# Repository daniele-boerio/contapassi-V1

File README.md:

# Setup Claude Code — contapassi

## Struttura del repo

```
contapassi/
├── .claude/
│   ├── CLAUDE.md                       ← contesto sempre caricato
│   └── skills/
│       ├── kicad-jlcpcb/SKILL.md
│       ├── nrf52840-firmware/SKILL.md
│       └── analisi-andatura/SKILL.md
├── .gitignore
├── README.md
│
├── docs/
│   ├── 01-design.md
│   ├── 02-bom-jlcpcb.md
│   ├── 03-firmware-taratura.md
│   └── datasheet/              ← E73, LSM6DSV16X, MCP73831, cella
│
├── hardware/
│   ├── contapassi.kicad_pro
│   ├── contapassi.kicad_sch
│   ├── contapassi.kicad_pcb
│   ├── lib/
│   │   ├── contapassi.kicad_sym
│   │   ├── contapassi.pretty/  ← footprint
│   │   └── 3dmodels/
│   └── production/
│       └── 2026-XX-XX-v1/      ← gerber + BOM + CPL di ogni ordine
│
├── firmware/
│   ├── CMakeLists.txt
│   ├── prj.conf
│   ├── boards/                 ← definizione board custom
│   └── src/
│
├── analysis/
│   ├── notebooks/
│   ├── src/                    ← parser, ZUPT, metriche
│   └── data/
│       ├── raw/                ← dump binari (NON versionati)
│       └── ground-truth.csv    ← versionato, è prezioso
│
└── ios/
```

### Le scelte che contano

**`lib/` va dentro `hardware/`.** KiCad risolve le librerie di progetto con
`${KIPRJMOD}`, che punta alla cartella del `.kicad_pro`. Fuori da lì i percorsi
si rompono appena sposti il progetto.

**Un solo repo, non tre.** Hardware, firmware e analisi cambiano insieme: se
sposti un pin nello schematico devi toccare anche il firmware. Con repo separati
quella correlazione si perde, e il CLAUDE.md andrebbe duplicato.

**`hardware/production/` con una cartella datata per ordine.** I file di
produzione sono generati, ma sono l'unica traccia di _cosa hai effettivamente
ordinato_. Quando la scheda arriva e qualcosa non torna, vuoi guardare i file
spediti — non rigenerarli da un progetto nel frattempo modificato.

**`firmware/boards/` non è opzionale.** L'nRF Connect SDK ha bisogno di una
definizione di board per il PCB custom: è lì che si dichiara quali pin sono SPI,
dove stanno gli interrupt e la configurazione del quarzo. È la traduzione in
codice della mappatura pin del doc 01.

**`analysis/data/raw/` fuori da git** — sono ~27 MB al giorno di dump, il repo
diventerebbe ingestibile in una settimana. Tienili in una cartella sincronizzata
o su un disco esterno.

**`ground-truth.csv` invece va versionato.** È piccolo e irripetibile: sono le
camminate fatte contando i passi a mano. Se lo perdi, rifai tutta la raccolta.

### .gitignore minimo

```gitignore
# KiCad
*-backups/
*.kicad_prl
*.bak
fp-info-cache
~*.*

# Firmware
build/

# Analisi
analysis/data/raw/
__pycache__/
.ipynb_checkpoints/
```

`.kicad_prl` è escluso ma `.kicad_pro` no: il primo contiene preferenze locali di
visualizzazione, il secondo le impostazioni di progetto da condividere.

## CLAUDE.md vs skill — la differenza

**CLAUDE.md** viene caricato in ogni conversazione. Contiene solo ciò che serve
sempre: cos'è il progetto, le decisioni congelate, i vincoli non negoziabili.
Tenerlo corto è importante — occupa contesto a ogni messaggio.

**Le skill** si caricano solo quando servono, in base alla loro `description`.
Contengono il dettaglio operativo di un dominio specifico. Le tre qui sono
disgiunte: hardware/produzione, firmware, analisi dati.

## Le tre skill

| Skill               | Si attiva su                                                    |
| ------------------- | --------------------------------------------------------------- |
| `kicad-jlcpcb`      | KiCad, schematico, PCB, footprint, BOM, CPL, componenti, ordini |
| `nrf52840-firmware` | Codice firmware, driver, BLE, interrupt, consumo, bring-up      |
| `analisi-andatura`  | Python, notebook, ZUPT, stance detection, taratura, validazione |

## Verifica che funzionino

In Claude Code, `/skills` elenca le skill disponibili. Se una non compare,
controlla che il frontmatter YAML sia valido e che `name` coincida con il nome
della cartella.

Per testare il triggering, prova richieste generiche e osserva se la skill si
attiva:

- "aggiungi un condensatore di bypass all'IMU" → `kicad-jlcpcb`
- "perché il consumo in idle è più alto del previsto?" → `nrf52840-firmware`
- "il conteggio passi sbaglia sulle camminate lente" → `analisi-andatura`

Se una skill non si attiva quando dovrebbe, il problema è quasi sempre nella
`description`: aggiungi i termini che l'utente userebbe realmente. Le descrizioni
sono volutamente "spinte" (elencano molti sinonimi e casi generici) proprio
perché la tendenza tipica è di non attivarle abbastanza.

## Manutenzione

Le skill contengono numeri che possono cambiare — budget energetico, quote,
codici LCSC. Quando un documento in `docs/` cambia, **controlla se la skill
corrispondente ripete quel numero**. Meglio ancora: dove possibile la skill
rimanda al documento invece di duplicare il valore.

I punti attualmente duplicati e da tenere allineati:

- budget ~161 µA e autonomia ~10 giorni (CLAUDE.md, firmware)
- quote PCB 24 × 41 mm (kicad-jlcpcb)
- codice LCSC del modulo `C356849` (CLAUDE.md, kicad-jlcpcb)
- configurazione IMU ±16 g / 416 Hz (firmware, analisi)

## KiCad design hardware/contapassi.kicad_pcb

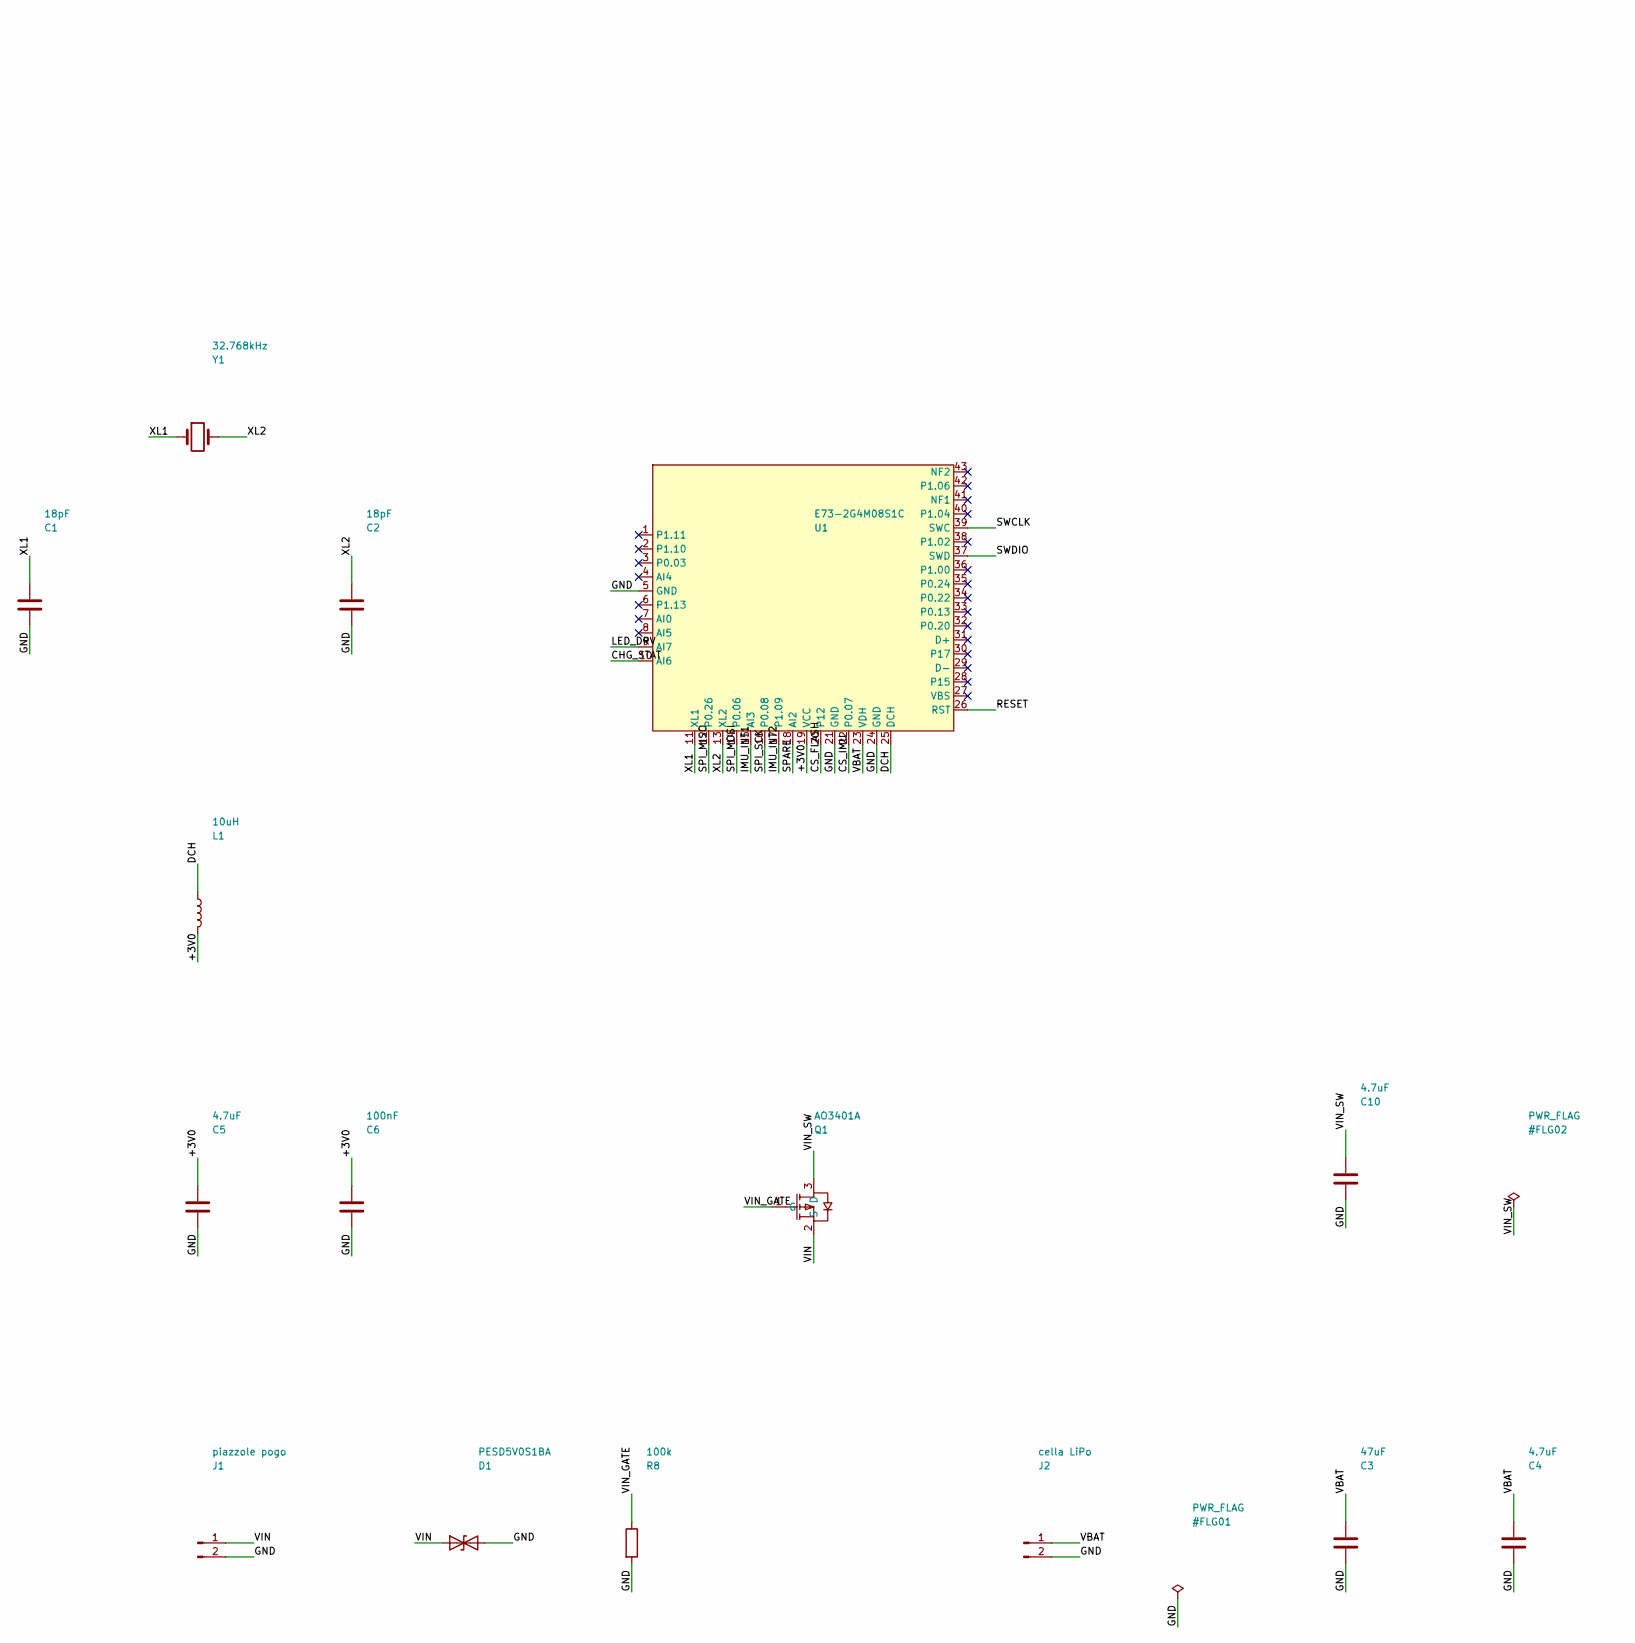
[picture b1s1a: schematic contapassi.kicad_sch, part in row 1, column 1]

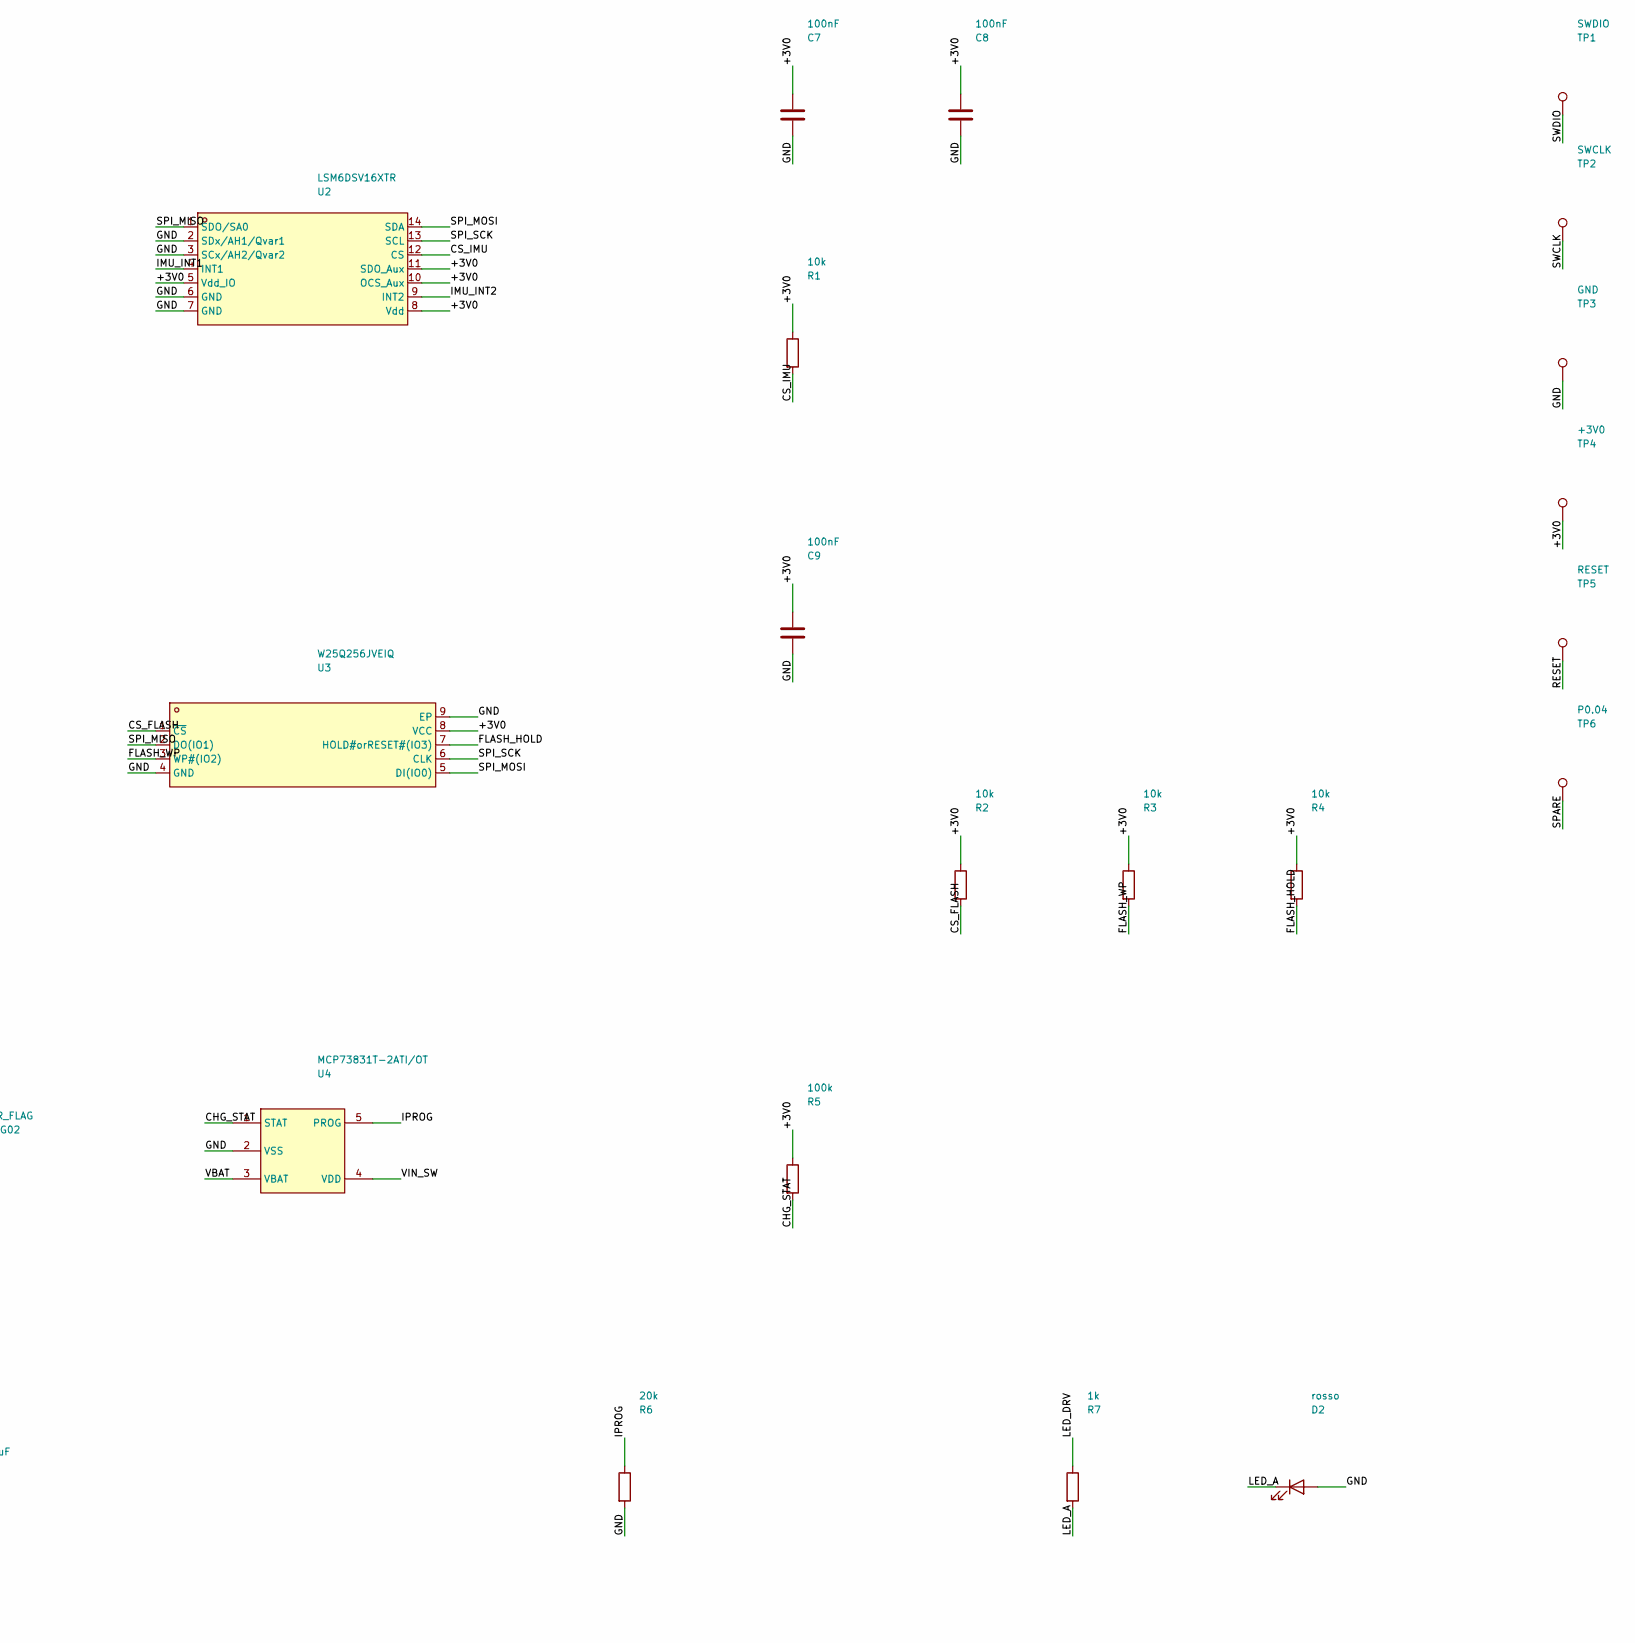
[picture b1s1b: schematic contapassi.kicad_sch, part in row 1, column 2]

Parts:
C1, C2: 18pF; C_0402_1005Metric; LCSC C1549
C3: 47uF; C_1206_3216Metric; LCSC C96123
C4, C5, C10: 4.7uF; C_0603_1608Metric; LCSC C19666
C6, C7, C8, C9: 100nF; C_0402_1005Metric; LCSC C1525
D1: PESD5V0S1BA; D_SOD-323; LCSC C2827694
D2: rosso; LED_0603_1608Metric; LCSC C2286
J1: piazzole pogo; PogoPads_2P_P5.0mm
J2: cella LiPo; CellPads_2P_P4.0mm
L1: 10uH; L_0603_1608Metric; LCSC C76798
Q1: AO3401A; SOT-23_L2.9-W1.3-P1.90-LS2.4-BR; LCSC C15127
R1, R2, R3, R4: 10k; R_0402_1005Metric; LCSC C25744
R5, R8: 100k; R_0402_1005Metric; LCSC C25741
R6: 20k; R_0402_1005Metric; LCSC C25765
R7: 1k; R_0402_1005Metric; LCSC C11702
TP1: SWDIO; TestPoint_Pad_1.5x1.5mm
TP2: SWCLK; TestPoint_Pad_1.5x1.5mm
TP3: GND; TestPoint_Pad_1.5x1.5mm
TP4: +3V0; TestPoint_Pad_1.5x1.5mm
TP5: RESET; TestPoint_Pad_1.5x1.5mm
TP6: P0.04; TestPoint_Pad_1.5x1.5mm
U1: E73-2G4M08S1C; WIRELM-SMD_E73-2G4M08S1C; LCSC C356849
U2: LSM6DSV16XTR; LGA-14_L3.0-W2.5-P0.50-BR; LCSC C5267406
U3: W25Q256JVEIQ; WSON-8_L8.0-W6.10-P1.27-BL-EP; LCSC C97522
U4: MCP73831T-2ATI/OT; SOT-23-5_L3.0-W1.7-P0.95-LS2.8-BR; LCSC C14879
Y1: 32.768kHz; Crystal_SMD_3215-2Pin_3.2x1.5mm; LCSC C32346

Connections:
+3V0: C5.1, C6.1, C7.1, C8.1, C9.1, L1.2, R1.1, R2.1, R3.1, R4.1, R5.1, TP4.1, U1.19 (VCC), U2.5 (Vdd_IO), U2.8 (Vdd), U2.10 (OCS_Aux), U2.11 (SDO_Aux), U3.8 (VCC)
CHG_STAT: R5.2, U1.10 (AI6), U4.1 (STAT)
CS_FLASH: R2.2, U1.20 (P12), U3.1 (~CS)
CS_IMU: R1.2, U1.22 (P0.07), U2.12 (CS)
DCH: L1.1, U1.25 (DCH)
FLASH_HOLD: R4.2, U3.7 (HOLD#orRESET#(IO3))
FLASH_WP: R3.2, U3.3 (WP#(IO2))
GND: C1.2, C2.2, C3.2, C4.2, C5.2, C6.2, C7.2, C8.2, C9.2, C10.2, D1.2 (A2), D2.2 (A), J1.2, J2.2, R6.2, R8.2, TP3.1, U1.5 (GND), U1.21 (GND), U1.24 (GND), U2.2 (SDx/AH1/Qvar1), U2.3 (SCx/AH2/Qvar2), U2.6 (GND), U2.7 (GND), U3.4 (GND), U3.9 (EP), U4.2 (VSS)
IMU_INT1: U1.15 (AI3), U2.4 (INT1)
IMU_INT2: U1.17 (P1.09), U2.9 (INT2)
IPROG: R6.1, U4.5 (PROG)
LED_A: D2.1 (K), R7.2
LED_DRV: R7.1, U1.9 (AI7)
RESET: TP5.1, U1.26 (RST)
SPARE: TP6.1, U1.18 (AI2)
SPI_MISO: U1.12 (P0.26), U2.1 (SDO/SA0), U3.2 (DO(IO1))
SPI_MOSI: U1.14 (P0.06), U2.14 (SDA), U3.5 (DI(IO0))
SPI_SCK: U1.16 (P0.08), U2.13 (SCL), U3.6 (CLK)
SWCLK: TP2.1, U1.39 (SWC)
SWDIO: TP1.1, U1.37 (SWD)
VBAT: C3.1, C4.1, J2.1, U1.23 (VDH), U4.3 (VBAT)
VIN: D1.1 (A1), J1.1, Q1.2 (S)
VIN_GATE: Q1.1 (G), R8.1
VIN_SW: C10.1, Q1.3 (D), U4.4 (VDD)
XL1: C1.1, U1.11 (XL1), Y1.1
XL2: C2.1, U1.13 (XL2), Y1.2

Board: 4 copper layers, 35 parts (0 on the bottom side), 26 nets, no tracks yet.
